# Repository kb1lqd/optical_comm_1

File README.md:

# optical_comm_1
Adventures in optical communications

# Lessons Learned

## Post PCB Order

Getting back into KiCAD after many years away and while focusing on my primary job and life has brought many challenges to this project. Here's the list of items I noted in the design and layout.

* I need a solid workflow for KiCAD for Symbols, Footprints, and library organization
  * I need a plan for how I want my own "Library" and process for making new boards/parts to lower the mental thought needed
  * Symbol checklist
  * Footprint Checklist
  * Sch/PCB Checklist
  * Create a template for OshPark 2/4 layer (and other vendors) to simplify future projects
* The scope of  this project ended up being quite large
* I had very little time outside of work/life to do this that intersected with my want to work on it
  * Break projects into small chunks
  * The multiplexing of jumping into this for an hour and out was very inefficient.
  * Lower the barrier to just getting a PCB in hand, refining my process, etc...
* I need more practice with KiCAD - it's different enough from Altium to be annoying and I'm not up for sitting through issues or planning after a day/week of work.

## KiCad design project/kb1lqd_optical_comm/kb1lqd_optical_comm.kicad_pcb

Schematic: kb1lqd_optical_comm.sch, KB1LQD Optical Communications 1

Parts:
D1: VLCS5830; LED_D5.0mm
H1, H2, H3, H4: MountingHole_Pad; MountingHole_4.3mm_M4_DIN965_Pad
J1, J3, J6: SJ1-3523N; CUI_SJ1-3523N; PARTREV 1.02
J2: SJ-2509N; CUI_SJ-2509N; PART_REV B
J4: Conn_01x04_Male; Molex_KK-254_AE-6410-04A_1x04_P2.54mm_Vertical
J5: Conn_01x02_Male; Molex_KK-254_AE-6410-02A_1x02_P2.54mm_Vertical
R1, R3, R4, R32: 0; R_0603_1608Metric
R2, R5, R6, R7: 10k; R_0603_1608Metric
SW1, SW2, SW3: EG1213; SW_EG1213

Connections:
+5V: J4.1, R5.2, SW3.2; also elsewhere on the board
/Headphone_Input/AUDIO_INPUT: J3.3; also elsewhere on the board
/Headphone_Input/AUDIO_OUTPUT: SW1.1; also elsewhere on the board
/LED Driver/AUDIO_INPUT: SW1.2; also elsewhere on the board
/LED Driver/LED_RTN: D1.1 (K), J5.1; also elsewhere on the board
/Michrophone Pre-Amp/AUDIO_INPUT: J1.3; also elsewhere on the board
/Michrophone Pre-Amp/AUDIO_OUTPUT: SW1.3; also elsewhere on the board
/Photodiode Transimpedance Amplifier/OUTPUT: SW2.3; also elsewhere on the board
/Sheet5FD6A4A6/IN1: SW2.2; also elsewhere on the board
/Sheet5FD6A4A6/IN2: R6.1; also elsewhere on the board
AUDIO_OUT1: J6.2, R32.2; also elsewhere on the board
AUDIO_OUT2: J6.3, R3.1, R7.1; also elsewhere on the board
GND: H1.1, H2.1, H3.1, H4.1, J2.1, J4.3, J6.1, R1.2, R2.2, R4.2, R6.2, R7.2; also elsewhere on the board
unnamed: D1.2 (A), SW3.1
unnamed: J1.1, R1.1
unnamed: J1.2, R5.1
unnamed: J2.2, R3.2
unnamed: J2.3, R32.1
unnamed: J3.1, R4.1
unnamed: J3.2, R2.1
unnamed: J4.2, SW2.1
unnamed: J5.2, SW3.3

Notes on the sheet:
3.5mm Connector Tip = V+ Ring = Mic+ Shield = Mic-
2.5mm Connector Tip = Speaker+ Ring = Unused Shield = GND
Electrect Bias May need tuning Set for 500uA @ 5V
ON-BOARD LED
EXTERNAL LED
NEEDS UPDATE TO CORRECT PN
External Photodiode (Amplified)
3.5mm Connector Tip = AUDIO_P Ring = OPEN Shield = AUDIO_N SJ1-3523N
EXTRA AUDIO INPUT
EXTRA AUDIO OUTPUT
3.5mm Connector Tip = AUDIO1 Ring = AUDIO2 Shield = GND SJ1-3523N
AUX 1/8" Output Audio
Kenwood Style Audio Jack
1/8" Jack Line Input

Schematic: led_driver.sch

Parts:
C1: 3.9n; C_0805_2012Metric
Q1: PMBF170; SOT-23
R8: 10k; R_0603_1608Metric
R9, R11: 3.2k; R_0603_1608Metric
R10: 1k; R_0603_1608Metric
R12: 140; R_0603_1608Metric
U1: AD8648; TSSOP-14_4.4x5mm_P0.65mm

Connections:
+5V: R9.1; also elsewhere on the board
/LED Driver/AUDIO_INPUT: R8.2; also elsewhere on the board
/LED Driver/LED_RTN: Q1.3 (D); also elsewhere on the board
GND: C1.2, R10.2, R12.2; also elsewhere on the board
unnamed 13: C1.1, R8.1, R9.2, R10.1; also elsewhere on the board
unnamed 40: Q1.1 (G); also elsewhere on the board
unnamed: Q1.2 (S), R11.1, R12.1
unnamed 42: R11.2; also elsewhere on the board

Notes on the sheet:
LED DRIVE OUTPUT
1.2V Reference
fc(3dB)= x
Id(max)=300mA Pd(Max)=830mW Rds(on)=5 Ohms Rth(j-a)= 350 K/W
Current Limit / Sense Resistor I(max) = 18mA
CHANGE TO 2 CHANNEL VERSION (SUPPORTS MIC/LED DRIVER)

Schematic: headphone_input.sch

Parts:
C2, C3: 1u; C_1206_3216Metric
C12: DNP; C_0805_2012Metric
C20: DNP; C_0201_0603Metric
R13: 10k; R_0603_1608Metric
R14, R16: 3.2k; R_0603_1608Metric
R15: 1k; R_0603_1608Metric
R17: 0; R_0603_1608Metric
RV1: 50k; Molex_KK-254_AE-6410-04A_1x04_P2.54mm_Vertical
U1: AD8648; TSSOP-14_4.4x5mm_P0.65mm

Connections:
+5V: C2.2, R14.1; also elsewhere on the board
/Headphone_Input/AUDIO_INPUT: RV1.3; also elsewhere on the board
/Headphone_Input/AUDIO_OUTPUT: C20.1, R16.1, R17.1; also elsewhere on the board
GND: C2.1, C12.2, R13.2, R15.2; also elsewhere on the board
unnamed: C3.2, R13.1, RV1.1, RV1.2
unnamed 21: C3.1, C12.1, R14.2, R15.1; also elsewhere on the board
unnamed 27: C20.2, R16.2; also elsewhere on the board
unnamed 43: R17.2; also elsewhere on the board

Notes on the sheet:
1.2V Reference
0-8Vp-p Input Range
Assumed input is able to adjust audio input level.
Maximum Needed Attenuation = 0.3V/V
Maximum Attenuation = 0.2V/V
PTV09A-4025F-B503

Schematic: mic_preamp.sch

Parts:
100k1: R_US
C4, C5, C7: 1u
C6, C21, C22: DNP
C23: 100nF
R18, R21: 3.24k
R19, R20, R22, R23, R24: 1k
RV2: 20k
U2: AD8648

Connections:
+5V: C4.2, C23.1, R18.2, R21.2, U2.8; also elsewhere on the board
/Michrophone Pre-Amp/AUDIO_INPUT: C5.2; also elsewhere on the board
/Michrophone Pre-Amp/AUDIO_OUTPUT: C22.1, RV2.1, U2.7; also elsewhere on the board
GND: C4.1, C21.2, C23.2, R19.1, R22.1, U2.4; also elsewhere on the board
unnamed: C5.1, R20.2
unnamed 16: 100k1.1, C6.1, C7.2, U2.1; also elsewhere on the board
unnamed 17: 100k1.2, C6.2, R20.1, U2.3; also elsewhere on the board
unnamed: C7.1, R23.2
unnamed: C21.1, R21.1, R22.2, U2.6
unnamed: C22.2, R23.1, R24.2, U2.5
unnamed: R18.1, R19.2, U2.2
unnamed: R24.1, RV2.2, RV2.3

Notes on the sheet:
AV=100V/V
AV= 1 to 21 V/V
1.2V single supply VREF
GBP = 240KHz
GBP = 2.0 MHz
Optional LPF

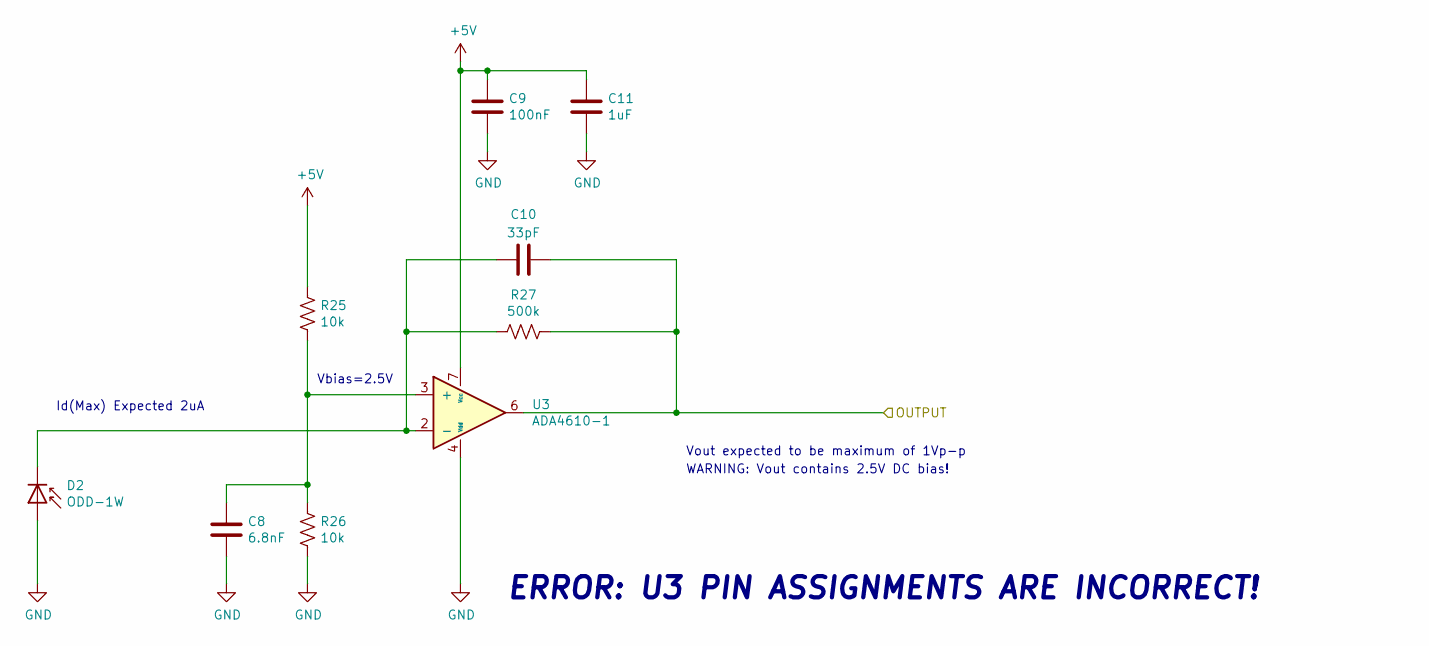
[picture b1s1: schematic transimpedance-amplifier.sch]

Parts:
C8: 6.8nF; C_0805_2012Metric
C9: 100nF; C_0805_2012Metric
C10: 33pF; C_0603_1608Metric
C11: 1uF; C_1206_3216Metric
D2: ODD-1W; TO-18-2
R25, R26: 10k; R_0603_1608Metric
R27: 500k; R_0603_1608Metric
U3: ADA4610-1; SOIC-8_3.9x4.9mm_P1.27mm

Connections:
+5V: C9.1, C11.1, R25.1, U3.7 (Vcc); also elsewhere on the board
/Photodiode Transimpedance Amplifier/OUTPUT: C10.1, R27.1, U3.6; also elsewhere on the board
GND: C8.2, C9.2, C11.2, D2.2 (A), R26.2, U3.4 (Vdd); also elsewhere on the board
unnamed: C8.1, R25.2, R26.1, U3.3 (+)
unnamed: C10.2, D2.1 (K), R27.2, U3.2 (-)

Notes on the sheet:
Id(Max) Expected 2uA
Vout expected to be maximum of 1Vp-p
Vbias=2.5V
WARNING: Vout contains 2.5V DC bias!
ERROR: U3 PIN ASSIGNMENTS ARE INCORRECT!

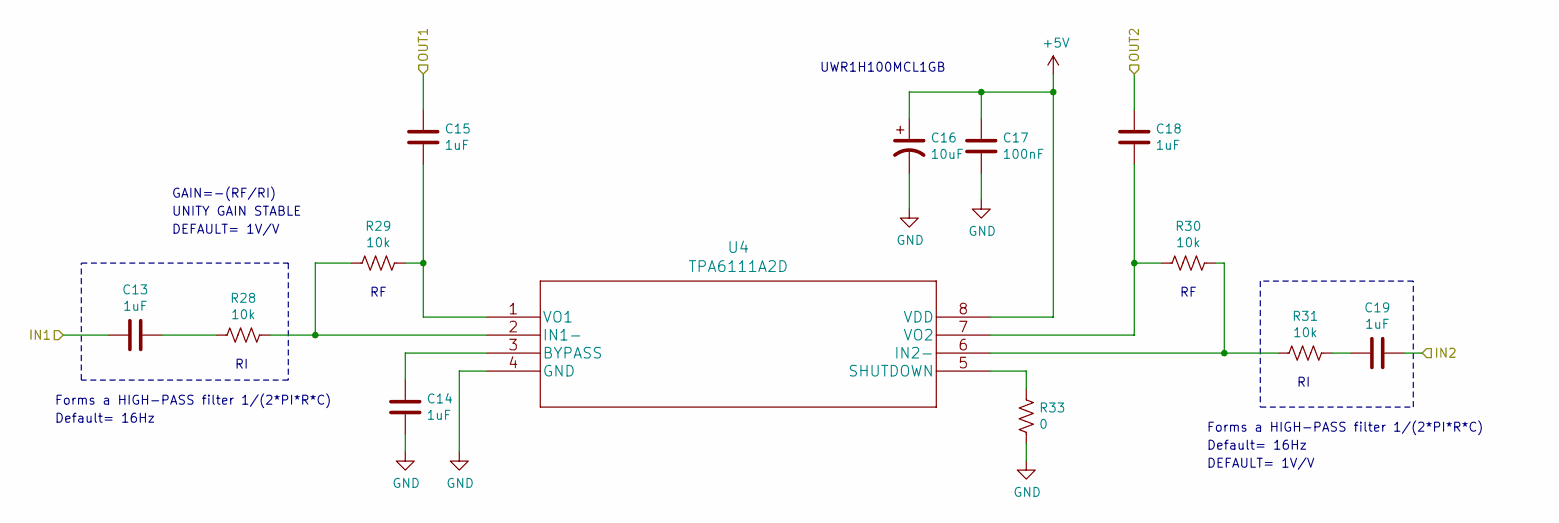
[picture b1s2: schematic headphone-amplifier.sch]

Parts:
C13, C14, C15, C18, C19: 1uF; C_1206_3216Metric
C16: 10uF; CP_Elec_5x5.3
C17: 100nF; C_0805_2012Metric
R28, R29, R30, R31: 10k; R_0603_1608Metric
R33: 0; R_0603_1608Metric
U4: TPA6111A2D

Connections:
+5V: C16.1, C17.2, U4.8 (VDD); also elsewhere on the board
/Sheet5FD6A4A6/IN1: C13.1; also elsewhere on the board
/Sheet5FD6A4A6/IN2: C19.2; also elsewhere on the board
AUDIO_OUT1: C15.2; also elsewhere on the board
AUDIO_OUT2: C18.2; also elsewhere on the board
GND: C14.1, C16.2, C17.1, R33.1, U4.4 (GND); also elsewhere on the board
unnamed: C13.2, R28.2
unnamed: C14.2, U4.3 (BYPASS)
unnamed: C15.1, R29.1, U4.1 (VO1)
unnamed: C18.1, R30.2, U4.7 (VO2)
unnamed: C19.1, R31.1
unnamed: R28.1, R29.2, U4.2 (IN1-)
unnamed: R30.1, R31.2, U4.6 (IN2-)
unnamed: R33.2, U4.5 (SHUTDOWN)

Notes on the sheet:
GAIN=-(RF/RI)
UNITY GAIN STABLE
Forms a HIGH-PASS filter 1/(2*PI*R*C)
Default= 16Hz
DEFAULT= 1V/V
UWR1H100MCL1GB

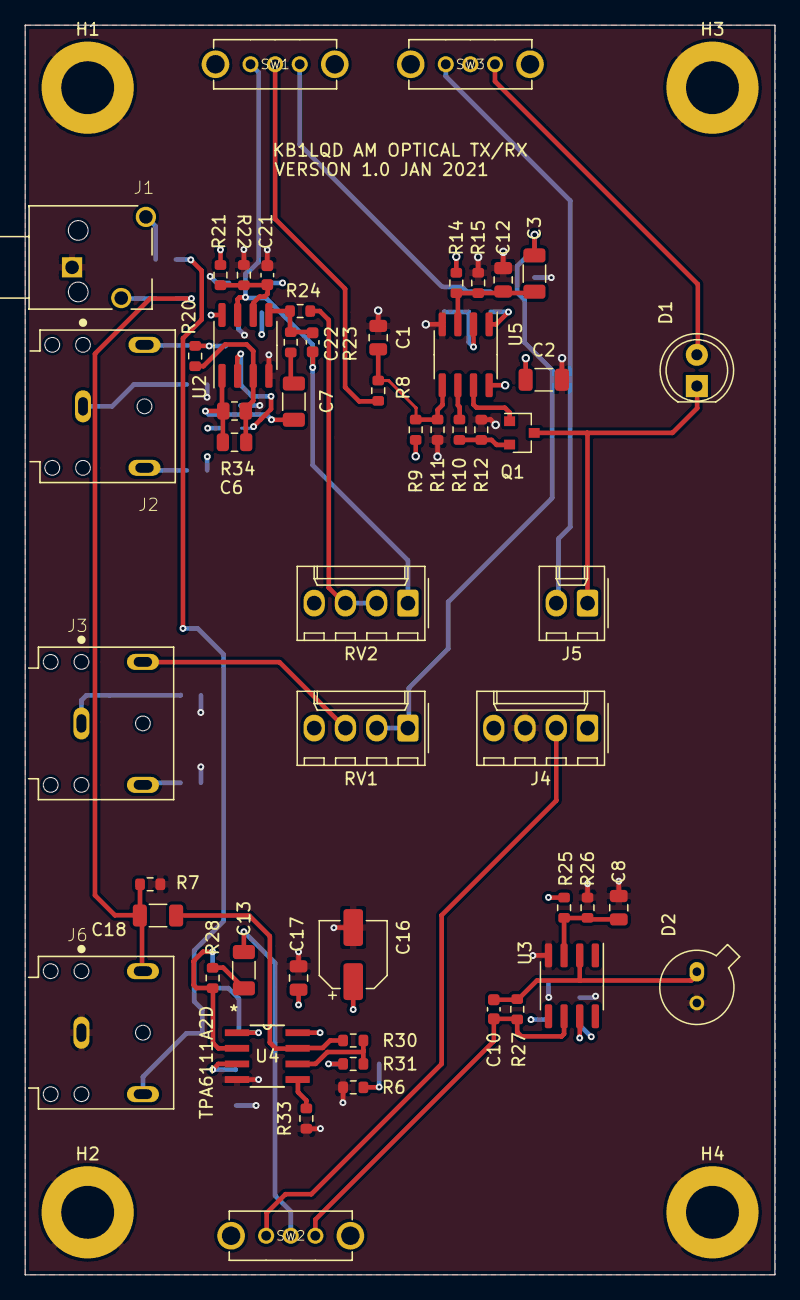
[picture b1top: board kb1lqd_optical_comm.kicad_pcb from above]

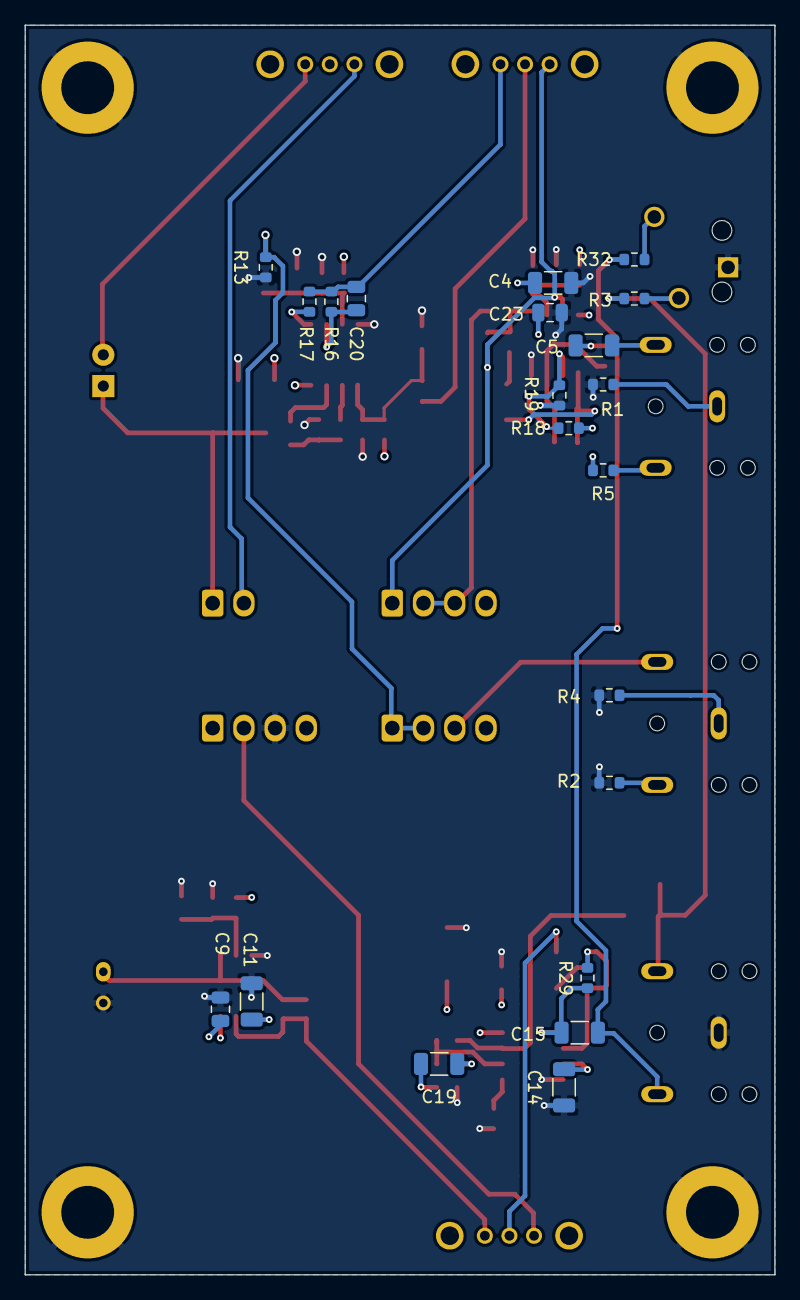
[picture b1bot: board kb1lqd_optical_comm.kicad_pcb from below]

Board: 4 copper layers, 61.0 x 101.6 mm, 79 parts (21 on the bottom side), 48 nets.

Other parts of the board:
R34: 100k; R_0805_2012Metric
U5: AD8646; SOIC-8_3.9x4.9mm_P1.27mm

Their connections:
+5V: U5.8; also elsewhere on the board
GND: U5.4; also elsewhere on the board
unnamed 13: U5.5; also elsewhere on the board
unnamed 16: R34.1; also elsewhere on the board
unnamed 17: R34.2; also elsewhere on the board
unnamed 21: U5.3; also elsewhere on the board
unnamed 27: U5.2; also elsewhere on the board
unnamed 40: U5.7; also elsewhere on the board
unnamed 42: U5.6; also elsewhere on the board
unnamed 43: U5.1; also elsewhere on the board

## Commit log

2020-08-30 Adding requirements.
2020-08-30 Updated requirements, added architectural design.
2020-09-07 Working current source
2020-09-07 Adding gitignore and oplot.
2020-09-07 Adding roughly complete transmitter, and notes.
2020-09-07 Spelling.
2020-09-07 Initial driver ipython.
2020-09-09 Updated mic pre-amp and output stage.
2020-09-14 Updating with RC filter, correct MOSFET.
2020-09-18 Adding KiCAD initial project.
2020-09-18 Adding AD8648 datasheet.
2020-09-19 Adding bode plot practice with ipython notebooks.
2020-09-21 Adding stability analysis for tx.
2020-09-21 Images.
2020-09-21 adding images correctly.
2020-09-21 Updated with better values and text.
2020-09-21 Adding updates.
2020-09-22 Adding updates for 9/21/2020
2020-09-22 Updated jack todo text.
2020-09-23 Adding audio jack symbols.
2020-09-23 Adding KK 100 series connector.
2020-09-23 Adding SPDT switch.
2020-09-23 Adding datasheets.
2020-11-15 Adding hand calculations designing optical receiver transimpedeance amplifier.
2020-12-13 adding recevier transimpedance amp. Adding simulations.
2020-12-13 Schematic essentially done.
2020-12-13 Fixing ERC errors.
2020-12-27 Updated with all footprints
2020-12-27 Updated with osh park board template rules.
2020-12-27 Initial placement mostly done. Outlined PCB.
2020-12-27 Initial placement condensed.
2020-12-27 More placement. Ready for board outline update.
2020-12-28 Placement done.
2020-12-28 Moved silkscreen references.
2020-12-28 Most of initial routing completed.
2020-12-28 More.
2021-01-01 Finished initial board. Downloaded audio jack footprint is causing errors on edge cut layer.
2021-01-01 No DRC errors.
2021-01-01 Updated mounting holes. Created BOM.
2021-01-04 Updated u2 to soic 8
2021-01-04 Updated to new soic footprint.
2021-01-05 Fixed a few errors in silkscreen, found an open item error in U3 generated footprint.
2021-02-04 Ordered this, checked U3 and other IC's and didn't find any issues...
2021-02-04 Adding lessons learned post PCB order.

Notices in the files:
parts and their libraries:
Copyright 2016 Accelerated Designs. All rights reserved.
